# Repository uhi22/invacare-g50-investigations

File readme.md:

# Invacare G50 Investigations

Investigating an electric wheel chair

## Progress

### 2025-01-07: DX-DASH Generation 2 ready for testing

The DX-DASH generation 2 consists of a board containing an STM32 controller, designed in KiCad,
a housing designed in FreeCad and the software designed in the STM CubeIDE.
The DX-DASH gen2 is controlling the Power Module, using either joystick or drive pedal and
direction switch.

[Instruction manual](doc/2025-01-06_DXDASH_installation_und_bedienung.md)

### 2024-10-15: STM32 simulates the UCM and the SLM

Simulating the UCM and the ServoLightModule, the STM32 is able to control
the motor speed directly.

### 2024-10-11: STM32 as UCM-replacement controls all functionality

The STM32 as UCM replacement controls a lot of functionality:
- Wakeup the other modules via the DXBUS
- Control the low beam light and the flashers
- Switch the power module into driving mode and back to idle mode
- Drive motor forwards and backwards using analog joystick input
- Turn the steering servo left and right using analog joystick input
- Send the power module and servo light module to sleep

### 2024-10-02: First spin

The STM32 sends all CAN messages to make the motor spin.

### 2024-09-30: Steering reacts

By sending some half-way proper CAN messages from the STM32 UCM replacement, the servo can be controlled to right-turn.
The motor disables the brake, but does not spin yet. It blinks 12 times.

### 2024-09-26: Controlling the lights works

Using the STM32 "blue pill" and a CAN transceiver, we control the lights via CAN. Due to the disconnected UCM,
the motor controller is stuck in state 0C, and the ServoLightModule in state 0. But nevertheless, low beam and
the turn indicators can be perfectly controlled with a 20ms message "0x040 B0 14 xx".
The ServoLightModule works even with very low battery voltage of 10V in this situation.

### 2024-09-24: STM32 interprets some network variables

Using the STM32 and attached display, we decode some network variables out of the CAN messages,
and show them on the display. 

## Goals

1. Understand the communication on the DX-BUS
2. Replace the original joystick ("UCM") by a self-made box which can control the motor, the lights and the steering.
3. Replace the UCM and the ServoLightModule by a self-made box to control only the motor.

## Pinout of the Power Module

The "Power Module" is a DX-PMB2-SAS, producer "Dynamic Controls", this seems to be the same as the DX-PMB2 mentioned in Ref1.

## Bus Communication

The "DXBUS" consists of four pins:
* Ground
* 24V
* CANH
* CANL

The ground and 24V are directly connected to the battery pins of the power module.

CAN bit time is 9.5µs, this means the CAN baud rate is 105.26 kBaud.
This baud rate can be created (according to STM32 cube IDE) with prescaler=57, T1=3, T2=2, SJW=1, TQ=1583.3ns, bittime=9500ns, 6 TQ per bit, inputClock=36MHz.

### CAN messages

UCM transmit messages (found by adding a separate CAN transceiver to the UCMs CAN_TX line):

* 0x040: The main data message. Contains lot of different sub-data.
* 0x0AA: not very interesting. Always "AA 04".
* 0x29C: "03 00 1A" during run. While turning off, "03 00 10".
* 0x2B4: Constant besides a toggle bit
* 0x2BC: nearly constant, only the last byte changes sometimes.
* 0x3A4: nearly constant, only the last byte changes during shutdown.
* 0x3AC: constant "03 00 1D"

ServoLightingModule transmit messages (found by adding a separate CAN transceiver to the ServoLightingModule CAN_TX line):

* 0x010 is the only transmit message. It contains various sub-messages, e.g.
    * 30 08 00 01 after startup
    * "B0 01 00" and "B0 01 02"
    * "10 00 ....", "12 00 ..."
    * and more

MotorModule transmit messages (all remaining messages which do not come from UCM and ServoLightingModule)
* 0x008 is the only transmit message. It contains various sub-messages, e.g.
    * A3, A1, A4 after startup
    * B0 01 02
    * B0 01 10 0F ...
    * B0 01 10 0C ...
    * B0 01 20 ...
    * B0 01 22
    * B0 01 25 
    * B0 0E ...
    * 30 02 ...
    * and more

```
0x008 B0 01 20 0C B5 0F FF
                   |
                   depends on the supply voltage. A7=22V, B6=24V, C6=26V. 150=19.8V, 200=26.5V 

0x040 B0 93 E1 00 14 00
                      |
                      lights 00=off, 11=light, 02/22 blinker right, 04/44 blinker left, 08/88 hazard flashing

0x040 B0 01 25 90 FF 80
                   |  |
                   |  joystick left/right. 01 is full left. 80 is middle. FF is full right.
                   joystick up/down. 01 is full backwards. 80 is middle, FF is full forward.
                   
0x2B4 03 00 0A
             |
             different values: 02, 0A. And 00 before power-off.

0x2BC 03 00 0F
             |
             different values: 0B, 0F. And 01 before power-off.
```

#### Message types

- First byte B0: "Network Variable announcement". After the B0 there is one byte NV_ID, followed by the content of the
network variable. The length depends on the ID. Afterwards, more {NV_ID, value} pairs may follow as long as there is space left in the CAN frame.
It is confirmed, that the same network variable can be on different position: The light control variable 14 works for controlling the lights in
the following frames in the same way:
    * 0x040 B0 93 E1 00 14 11
    * 0x040 B0 14 11

- First byte 30: "Wanna know". A node sends this message, to request network variable from other nodes.
```
   I'm the motor and...
   |   I wanna know...
   |   |  from node 2 (ServoLightModule)...
   |   |  |     the network variable 11
   |   |  |     |
0x008 30 02 00 11
```
The addressed node responds accordingly with the value of the requested network variable:
```
   I'm the ServoLightModule and...
   |   I want to announce my network variable...
   |   |  number 11...
   |   |  |   has the value 10.
   |   |  |  |
0x010 B0 11 10
```

After the variable number in the "30" message, there is sometimes more data, sometimes not. E.g. "03". Unclear: Is this an additional
network variable number? Or is it a kind of "request type" which selects the cycle time or number of responses or on/off?

- First byte 31: "unsubscribe". Tells the addressed note that it does not need to send the network variable anymore. E.g.
```
   I'm the ServoLightModule and...
   |   I do not need...
   |   |  from node 8 (UCM)...
   |   |  |     the network variable 2E
   |   |  |     |
0x010 31 08 00 2E
```
After this unsubscription, the UCM stops the cyclic transmission of NV 2E.

- First byte 20: unclear. Used in the first messages after startup. 4297725430,00000040,false,Rx,9,8,20,00,00,08,00,00,00,00,
- First byte 23: unclear. E.g. 00000040,false,Rx,9,8,23,00,00,08,FC,80,00,00. Responded by A3.
- First byte 21: similar to 23
- First byte 24: similar to 23

Request-response:
* 4297804953,00000040,false,Rx,9,8,23,00,00,08,FC,80,00,00,  request from the UCM
* 4297805609,00000008,false,Rx,9,1,A3                        response from Motor, where A3 seems to be the response to 23
* 4297806161,00000010,false,Rx,9,1,A3                        response from Servo, where A3 seems to be the response to 23
(and repeated)

again with other number:
* 4297818227,00000040,false,Rx,9,8,21,00,00,08,FC,80,00,00,  request from the UCM
* 4297818888,00000008,false,Rx,9,1,A1                        response from Motor
* 4297819437,00000010,false,Rx,9,1,A1                        response from Servo
(and repeated)

again with other number:
* 4297830564,00000040,false,Rx,9,8,24,00,00,08,FC,40,00,00,  request from the UCM
* 4297832560,00000008,false,Rx,9,1,A4                        response from Motor
* 4297832579,00000010,false,Rx,9,1,A4                        response from Servo
(and repeated)

### Profile changes

If the user changes the driving profile ("gear"), e.g. from 2 to 3, this results in
1. 040: B0,93,63,00,14,00 (once) The UCM announces profile 3.
2. 040: B0,93,E3,00 (repeated each 200ms) The UCM announces profile 3 in an other way.
3. 010: 30,08,00,2C The servo light module requests from the UCM the NV 2C.
4. 040: B0,93,E3,00,14,00,2C,66 UCM provides the NV 2C. Repeated after 200ms.
5. 010: 31,08,00,2C The servo light module stops the subscription of NV 2C.
6. The request/response/unsubscribe continues for other variables.

The end speed (at full joystick way) is parametrized separately for forward and reverse directions. Example profiles,
to demonstrate the speed influence of NV 2C (forward speed) and NV 2F (reverse speed):

```
		/* profiles:
		  1     2     3     4     5  */
		0x10, 0x59, 0x66, 0x73, 0xff, /* NV 0x2C */ /* max speed fwd. 10=very low, ff=high speed */
		0x66, 0x66, 0x73, 0x80, 0x80, /* NV 0x2D */
		0x20, 0x80, 0x80, 0x80, 0x80, /* NV 0x2E */
		0x10, 0x66, 0x66, 0x66, 0xff, /* NV 0x2F */ /* max speed reverse. 10=very low, ff=high speed */
		0x66, 0x66, 0x73, 0x80, 0x80, /* NV 0x30 */
		0x99, 0x99, 0x99, 0x99, 0x99, /* NV 0x31 */
		0xCC, 0xCC, 0xCC, 0xCC, 0xCC, /* NV 0x32 */
		0xB3, 0xB3, 0xB3, 0xB3, 0xB3, /* NV 0x33 */
		0x33, 0x33, 0x4D, 0x4D, 0x4D, /* NV 0x34 */
		0x80, 0x80, 0x99, 0xA6, 0xA6, /* NV 0x35 */
```

These profiles are used only by the ServoLightModule. The motor module is not interested into these profiles. The motor
module is controlled by network variable 0B, which the ServoLightModule provides.

### Error Codes

The PowerModule provides with the network variable 07 some error information:
- 00: no error. No blink code on the UCM.
- 0C: uncoupled the G40 motor. Blink code 3 on the UCM.
- 10: Motor M1 disconnected. Blink code 5 on the UCM.
- (more to be tested)

To use this error reporting, the NV 07 needs to be requested once at the beginning:
`00000010,false,Rx,9,4,30,01,00,07`

## The Wakeup

As long as the system is "off", the DX-BUS still carries 24V battery voltage, and both CAN lines are sitting at ~2.5V.
The system is activated when the user pushes the on/off button on the joystick module ("UCM"). The UCM wakes the other
control units by pulling the CANH to 24V for ~40ms. Afterwards, the UCM sends CAN traffic to keep the other control units
awake. If we apply just the wakeup pulse and do not send any CAN messages, the control units go to sleep again after five seconds.

## The Go-To-Sleep

If the user pushes the on/off button while the system is running, the UDS sends some special messages to send the other control
units to sleep, and stops the CAN communication. (Todo: Details to be described.)
If we just stop sending any messages from the UCM, the ServoLightModule enters an "emergency mode" after some seconds, where
it activats the hazard-flashing.

## Using the ServoLightModule standalone

The ServoLightModule can be used without the PowerModule to control the lights and the steering servo. Several aspects need to be considered to make this work.

1. The CAN termination. The absence of the PowerModule causes a missing CAN termination. We need to add a 510 ohm (or 470ohm) between
CANH and CANL. Additionally, we need a pull-up of the CANH via a diode and 390ohms (in series) to 3.3V, because the CAN transceiver inside
the SLM seems not to be capable of driving the CANH to high; it only pulls the CANL to low. So without additional pull-up on CANH,
a normal CAN transceiver is not able to pick-up the messages of the SLM.

2. The light control. This is the easy part. The SLM listens to the network variable 0x14, which we can announce e.g. with a message `0x040 B0 93 E1 00 14 00`. The light control bits are explained above. The SLM does not need to see the PowerModule for this functionality.

3. The steering servo control. This part is more tricky. To make the steering function work, the SLM needs to see the PowerModule and needs
to go through the corrects states.

    - The UCM and PowerModule must simulate the 23/A3, 21/A1 and 24/A4 sequences during startup.
    - The PowerModule must send the status after the SLM requests it with 010 30 01 00 01.
    - The PowerModule must send the network variables 0F, 0E and 07 after the SLM requested it with 010 30 01 00 0F or 010 30 01 00 0E or 010 30 01 00 07. If the SLM does not receive them, it changes from state 10 (init) to state 0C (error).
    - Even if the SLM now removes the steering brake when entering state 0x25, still the steering only works sporadically. To be further investigated.

## UCM (Joystick Control Module)

CAN_TX: Is the pin 1 of the 74HC02 on the sub-board.

### Diagnostic Connector

according to ref1, this is RS232.

## The Motor Controller (Power Module, PM)

Pinout: 

Motor PWM control:

Park brake control:

* The black park brake wire is grounded.
* The yellow park brake wire is switched to 24V to release the brake. Each 200ms, the PM turns the park brake off for 250µs, most likely for diagnotic purposes.

Current consumption:

* in sleep: 600µA. This means, a 20Ah usable battery capacity lasts for more than 3 years.

## The Motor

* Does does a motor of a G40 work at the motor controller of the G50? Yes.
* How does the "manual clutch switch" work?
    * In the G50 motor, when the user actuates the clutch to push the chair manually, the motor-integrated switch disconnects the *park brake magnet*.
    * In the G40plus motor, the motor integrated switch directly disconnects the *motor*.

## Self-made DXBUS controller

An STM32 development board ("blue pill"), combined with a ILI9341 TFT display and a SN65HVD230 CAN transceiver board and some small additions
is used to send and receive the CAN messages on the DXBUS, and also to send the wakeup pulse.

The 3D model for the printed DXBUS plug is available as [FreeCad model](3d_models/DXBUS_plug.FCStd) and [step file](3d_models/DXBUS_plug.step).

The software (as STM CubeIDE project) is available [here](stm32-tft).

## Open Todos

- [ ] ServoPos shows permanent 0
- [ ] add direction switch and pedal input
- [ ] implement special case "power button during driving"
- [ ] improve CAN scheduling to avoid message losses

## Finished Todos

- [x] Send NV 92 with FF FF in 200ms cycle
- [x] Send the profile (e.g. NV 93 = E1 00)
- [x] Send the parameters of the profile (NVs 2C to 35), after the ServoLight 0x010 requested it, e.g.
    - servoLight requests the 2C from UCM with 00000010,false,Rx,9,4,30,08,00,2C
    - ...
    - servoLight requests the 2E from UCM with 00000010,false,Rx,9,4,30,08,00,2E
    - more general: UCM needs to satisfy all requests (search for 30,08,00)
- [x] Find out how to parametrize the speed
- [x] Reset the CAN controller if it enters bus-off
- [x] Implement UCM start/idle/drive/idle/shutdown state machine
- [x] implement emulation of ServoLightModule, to be able to run the motor control unit without physical ServoLightModule

## Cross References

* [Ref1] System manual for the DXBUS https://www.dynamiccontrols.com/sites/default/files/2018-05/dx-system-manual-issue1.pdf
* [Ref2] European Patent EP0725738A1 (year 1993) https://patents.google.com/patent/EP0725738A1/en
* [Ref3] European Patent EP0725738B1 (year 1993), including schematics, state machines, some network variables. https://patents.google.com/patent/EP0725738B1/en
* [Ref4] SavvyCAN open source CAN logging tool https://www.savvycan.com/
* [Ref5] wifican CAN adaptor via wifi. Adapted to support the 105kBaud of the DXBUS. https://github.com/uhi22/wifican/commit/1e717946a06a594cf2e79b092cbaf7b376e8bb55
* [Ref6] pictures and document collection for the Invacare G50 https://hnng.de/invacare-g50/
* [Ref7] Master Thesis of Markus Schuch / Technikum Wien including a good overview over different wheel chair concepts, and a raspberry-pi based CAN "man in the middle" approach for the DXBUS. https://epub.technikum-wien.at/urn/urn:nbn:at:at-ftw:1-39670

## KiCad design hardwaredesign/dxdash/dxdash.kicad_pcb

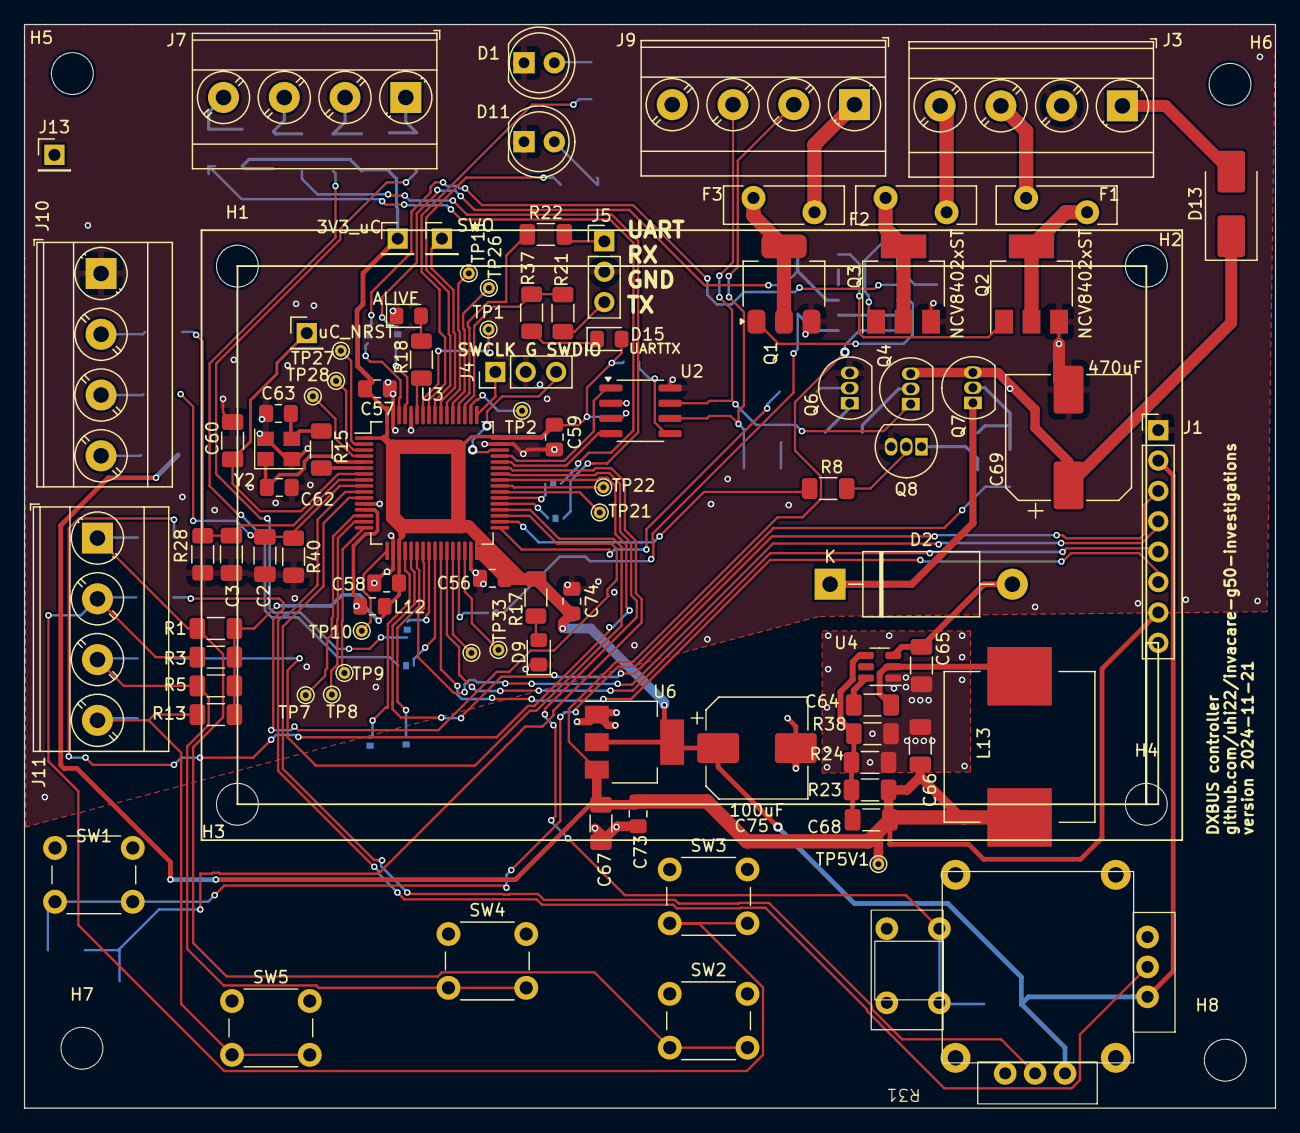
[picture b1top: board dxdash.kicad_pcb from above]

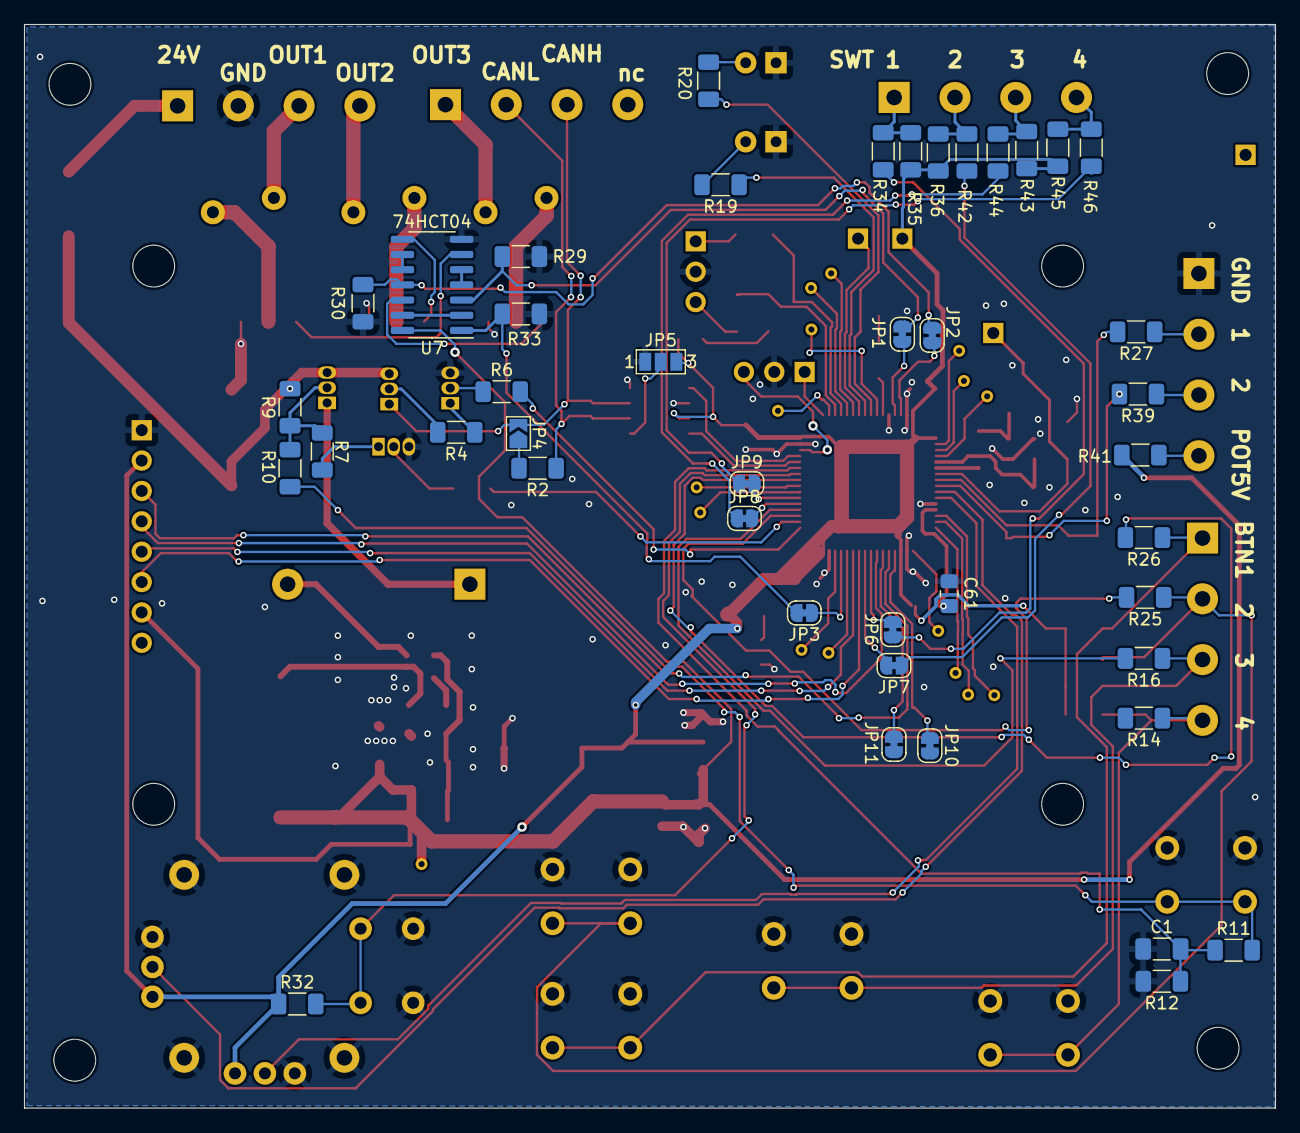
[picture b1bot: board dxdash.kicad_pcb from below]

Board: 2 copper layers, 104.6 x 90.6 mm, 143 parts (43 on the bottom side), 112 nets.

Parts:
C1: 100n; C_1206_3216Metric_Pad1.33x1.80mm_HandSolder
C2, C3, C60, C64: 100nF; C_1206_3216Metric_Pad1.33x1.80mm_HandSolder
C56, C57, C58, C59, C61, C73, C74: 100nF; C_0805_2012Metric_Pad1.18x1.45mm_HandSolder
C62, C63: 22p; C_0805_2012Metric_Pad1.18x1.45mm_HandSolder
C65: 10uF; C_1206_3216Metric_Pad1.33x1.80mm_HandSolder
C66, C67: 22uF; C_1206_3216Metric_Pad1.33x1.80mm_HandSolder
C68: 68pF; C_1206_3216Metric_Pad1.33x1.80mm_HandSolder
C69: 470uF; CP_Elec_10x10
C75: 100uF; CP_Elec_8x10
D1, D11: LED2; LED_D5.0mm
D2: Zener 5V; D_DO-201_P15.24mm_Horizontal
D9: PWR; LED_0805_2012Metric_Pad1.15x1.40mm_HandSolder
D10: ALIVE; LED_0805_2012Metric_Pad1.15x1.40mm_HandSolder
D13: SS54B-HF; D_SMB_Handsoldering
D15: UARTTX; LED_0805_2012Metric_Pad1.15x1.40mm_HandSolder
F1, F2, F3: Polyfuse; Fuse_Bourns_MF-RG400
H1, H2, H3, H4, H5, H6, H7, H8: MountingHole; MountingHole_3.5mm
J1: Conn_01x08_Pin; PinHeader_1x08_P2.54mm_Vertical
J3, J7, J9, J10, J11: Screw_Terminal_01x04; TerminalBlock_Phoenix_MKDS-3-4-5.08_1x04_P5.08mm_Horizontal
J4: DEBUG; PinHeader_1x03_P2.54mm_Vertical
J5: UART; PinHeader_1x03_P2.54mm_Vertical
J13: Conn_01x01_Pin; PinHeader_1x01_P2.54mm_Vertical
J16: uC_NRST; PinHeader_1x01_P2.54mm_Vertical
J17: 3V3_uC; PinHeader_1x01_P2.54mm_Vertical
J18: SWO; PinHeader_1x01_P2.54mm_Vertical
JP1, JP2, JP3, JP6, JP7, JP8, JP9, JP10, JP11: SolderJumper_2_Bridged; SolderJumper-2_P1.3mm_Bridged_RoundedPad1.0x1.5mm
JP4: SolderJumper_2_Open; SolderJumper-2_P1.3mm_Open_TrianglePad1.0x1.5mm
JP5: SolderJumper_3_Open; SolderJumper-3_P1.3mm_Open_Pad1.0x1.5mm_NumberLabels
L12: Bead 600; L_0805_2012Metric_Pad1.15x1.40mm_HandSolder
L13: 10uH; L_Wuerth_WE-PD-Typ-LS_Handsoldering
Q1, Q2, Q3: NCV8402xST; SOT-223
Q4, Q7: BC556; TO-92_Inline
Q6, Q8: BC546; TO-92_Inline
R1, R3, R4, R5, R6, R8, R11, R12, R13, R29, R30, R32, R33, R35, R36, R43, R45: 10k; R_1206_3216Metric_Pad1.30x1.75mm_HandSolder
R2, R17, R18, R19, R20, R37: 1k; R_1206_3216Metric_Pad1.30x1.75mm_HandSolder
R7, R9, R10: 4k7; R_1206_3216Metric_Pad1.30x1.75mm_HandSolder
R14, R16, R25, R26, R27, R28, R34, R39, R40, R42, R44, R46: 47k; R_1206_3216Metric_Pad1.30x1.75mm_HandSolder
R15: 33; R_1206_3216Metric_Pad1.30x1.75mm_HandSolder
R21, R22: 220; R_1206_3216Metric_Pad1.30x1.75mm_HandSolder
R23: 100k; R_1206_3216Metric_Pad1.30x1.75mm_HandSolder
R24: 33k; R_1206_3216Metric_Pad1.30x1.75mm_HandSolder
R31: Joystick; joystickXYButton
R38: 22k; R_1206_3216Metric_Pad1.30x1.75mm_HandSolder
R41: 100; R_1206_3216Metric_Pad1.30x1.75mm_HandSolder
SW1, SW2, SW3, SW4, SW5: SW_Push; SW_PUSH_6mm_H5mm
TP1, TP2, TP7, TP8, TP9, TP10, TP11, TP21, TP22, TP25, TP26, TP27, TP28, TP29, TP33: TestPoint_THTPad_D1.0mm_Drill0.5mm
TP5V1: TP5V; TestPoint_THTPad_D1.0mm_Drill0.5mm
U2: SN65HVD234; SOIC-8_3.9x4.9mm_P1.27mm
U3: STM32F103RETx; LQFP-64_10x10mm_P0.5mm
U4: TPS54302; SOT-23-6
U6: AMS1117-3.3; SOT-223-3_TabPin2
U7: 74HCT04; SO-14_3.9x8.65mm_P1.27mm
Y2: 8MHz; Crystal_SMD_TXC_7M-4Pin_3.2x2.5mm

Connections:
3V3_uC: C56.2, C57.2, C58.2, C59.2, C74.2, C75.1, D15.2 (A), J1.2, J17.1, JP5.3 (B), L12.2, R1.1, R3.1, R5.1, R13.1, R17.1, R31.1 (X1), R31.4 (Y1), R32.1, R35.1, R36.1, R43.1, R45.1, U2.3 (VCC), U3.1 (VBAT), U3.19 (VDD), U3.32 (VDD), U3.48 (VDD), U3.64 (VDD), U6.2 (VO)
5V: C66.2, C67.2, C68.2, C73.2, J1.7, L13.2, R23.1, R41.2, TP5V1.1, U6.3 (VI), U7.14 (VCC)
24V: D13.2 (A), J3.1
24V_P: C69.1, D13.1 (K), Q4.3 (E), Q7.3 (E), R9.2
24V_SWITCHED: C65.2, D2.2 (A), U4.3 (VIN)
/controller/OCS_IN: C62.2, U3.5 (PD0), Y2.1
/controller/OSC_OUT: R15.2, U3.6 (PD1)
BUSWAKE: R6.2, U3.33 (PB12)
CANH: J9.3, JP4.2 (B), Q4.1 (C), U2.7 (CANH)
CANL: J9.2, R2.1, U2.6 (CANL)
CAN_RX: U2.4 (R), U3.44 (PA11)
CAN_TX: U2.1 (D), U3.45 (PA12)
DISPLAY_DC: J1.6, U3.26 (PB0)
DISPLAY_RES: J1.5, U3.27 (PB1)
GND: C1.1, C2.2, C3.2, C56.1, C57.1, C58.1, C59.1, C60.1, C61.1, C62.1, C63.1, C65.1, C66.1, C67.1, C69.2, C73.1, C74.1, C75.2, D1.1 (K), D9.1 (K), D10.1 (K), D11.1 (K), J1.1, J3.2, J4.2, J5.2, J10.1, JP5.1 (A), Q1.3 (S), Q2.3 (S), Q3.3 (S), Q6.3 (E), Q8.3 (E), R12.2, R24.1, R28.1, R29.2, R30.1, R31.3 (X2), R31.6 (Y2), R31.9 (B2), R31.10 (B2.2), R31.11 (GND), R31.12 (GND), R31.13 (GND), R31.14 (GND), R33.2, R38.1, R40.1, SW1.1, SW2.1, SW3.1, SW4.1, SW5.1, U2.2 (GND), U2.8 (Rs), U3.12 (VSSA), U3.18 (VSS), U3.31 (VSS), U3.47 (VSS), U3.60 (BOOT0), U3.63 (VSS), U4.1 (GND), U6.1 (GND), U7.7 (GND), Y2.2, Y2.4
KEEP_ON: R8.2, U3.34 (PB13)
LED2: R19.1, U3.56 (PB4)
LED3: R20.1, U3.57 (PB5)
LED_ALIVE: R18.1, U3.59 (PB7)
unnamed: C63.2, R15.1, Y2.3
unnamed: D1.2 (A), R20.2
unnamed: D2.1 (K), Q7.1 (C)
unnamed: D9.2 (A), R17.2
unnamed: D10.2 (A), R18.2
unnamed: D11.2 (A), R19.2
unnamed: D15.1 (K), R37.2
unnamed: F1.1, Q2.2 (D), Q2.4 (D)
unnamed: F2.1, Q3.2 (D), Q3.4 (D)
unnamed: F3.1, Q1.2 (D), Q1.4 (D)
unnamed: J5.1, R22.2
unnamed: J5.3, R21.2
unnamed: JP1.1 (A), U3.61 (PB8)
unnamed: JP2.1 (A), U3.62 (PB9)
unnamed: JP3.1 (A), U3.29 (PB10)
unnamed: JP4.1 (A), R2.2
unnamed: JP5.2 (C), U2.5 (EN)
unnamed: JP6.2 (B), U3.24 (PC4)
unnamed: JP7.2 (B), U3.25 (PC5)
unnamed: JP8.2 (B), U3.37 (PC6)
unnamed: JP9.2 (B), U3.38 (PC7)
unnamed: Q1.1 (G), U7.12
unnamed: Q2.1 (G), U7.6
unnamed: Q3.1 (G), U7.8
unnamed: Q4.2 (B), R4.2
unnamed: Q6.2 (B), R6.1
unnamed: Q6.1 (C), R4.1
unnamed: Q7.2 (B), R7.2, R9.1, R10.1
unnamed: Q8.2 (B), R8.1
unnamed: Q8.1 (C), R7.1
unnamed: R10.2, R11.2, SW1.2
unnamed: TP7.1, U3.14 (PA0)
unnamed: TP8.1, U3.15 (PA1)
unnamed: TP9.1, U3.16 (PA2)
unnamed: TP10.1, U3.17 (PA3)
unnamed: TP2.1, U3.50 (PA15)
unnamed: TP25.1, U3.28 (PB2)
unnamed: TP1.1, U3.58 (PB6)
unnamed: TP33.1, U3.30 (PB11)
unnamed: TP21.1, U3.39 (PC8)
unnamed: TP22.1, U3.40 (PC9)
unnamed: TP26.1, U3.53 (PC12)
unnamed: TP27.1, U3.2 (PC13)
unnamed: TP28.1, U3.3 (PC14)
unnamed: TP29.1, U3.4 (PC15)
unnamed: TP11.1, U3.54 (PD2)
unnamed: C61.2, L12.1, U3.13 (VDDA)
unnamed: C64.2, U4.6 (BOOT)
unnamed: C68.1, R23.2, R24.2, R38.2, U4.4 (FB)
unnamed: C64.1, L13.1, U4.2 (SW)
unnamed: U7.4, U7.5
unnamed: U7.9, U7.10
unnamed: U7.2, U7.13
OUT1_LS: F1.2, J3.3
OUT2_LS: F2.2, J3.4
OUT3_LS: F3.2, J9.1
OUT_CONTROL1: JP1.2 (B), R29.1, U7.3
OUT_CONTROL2: JP2.2 (B), R30.2, U7.11
OUT_CONTROL3: JP3.2 (B), R33.1, U7.1
SPI1_CLK: J1.3, U3.21 (PA5)
SPI1_MISO: JP11.1 (A), U3.22 (PA6)
SPI1_MOSI: J1.4, U3.23 (PA7)
SPI1_NSS: JP10.1 (A), U3.20 (PA4)
SWCLK: J4.1, U3.49 (PA14)
SWDIO: J4.3, U3.46 (PA13)
SWO: J18.1, U3.55 (PB3)
UART4_RX: R22.1, U3.52 (PC11)
UART4_TX: R21.1, R37.1, U3.51 (PC10)
button1: J11.1, R1.2, R26.1, SW2.2
button2: J11.2, R3.2, R25.1, SW3.2
button3: J11.3, R5.2, R16.1, SW4.2
button4: J11.4, R13.2, R14.1, SW5.2
pot1: J10.2, R27.1
pot2: J10.3, R39.1
pot5V: J10.4, R41.1
switch1: J7.1, R34.1, R35.2
switch2: J7.2, R36.2, R42.1
switch3: J7.3, R43.2, R44.1
switch4: J7.4, R45.2, R46.1
uC_NRST: C60.2, J16.1, U3.7 (NRST)
uC_button1: R26.2, U3.41 (PA8)
uC_button2: R25.2, U3.35 (PB14)
uC_button3: R16.2, U3.36 (PB15)
uC_joystickX: R31.2 (XM), U3.10 (PC2)
uC_joystickY: R31.5 (YM), U3.11 (PC3)
uC_joystickbutton: R31.7 (B1), R31.8 (B1.2), R32.2, U3.42 (PA9)
uC_pot1: C3.1, R27.2, R28.2, U3.8 (PC0)
uC_pot2: C2.1, R39.2, R40.2, U3.9 (PC1)
uC_pwr_button: C1.2, R11.1, R12.1, U3.43 (PA10)
uC_switch1: JP6.1 (A), R34.2
uC_switch2: JP7.1 (A), R42.2
uC_switch3: JP8.1 (A), R44.2
uC_switch4: JP9.1 (A), R46.2

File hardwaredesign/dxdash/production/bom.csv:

Designator,Footprint,Quantity,Value,LCSC Part #
C1,1206,1,100n,C14663
"C2, C3, C60, C64",1206,4,100nF,C14663
"C56, C57, C58, C59, C61, C73, C74",0805,7,100nF,C14663
"C62, C63",0805,2,22p,C1679
C65,1206,1,10uF,C14663
"C66, C67",1206,2,22uF,C14663
C68,1206,1,68pF,C14663
C69,CP_Elec_10x10,1,470uF,
C75,CP_Elec_8x10,1,100uF,
"D1, D11",LED_D5.0mm,2,LED2,
D10,0805,1,ALIVE,
D13,D_SMB_Handsoldering,1,SS54B-HF,
D15,0805,1,UARTTX,
D2,D_DO-201_P15.24mm_Horizontal,1,Zener 5V,
D9,0805,1,PWR,
"F1, F2, F3",Fuse_Bourns_MF-RG400,3,Polyfuse,
J1,PinHeader_1x08_P2.54mm_Vertical,1,Conn_01x08_Pin,
"J10, J11, J3, J7, J9",TerminalBlock_Phoenix_MKDS-3-4-5.08_1x04_P5.08mm_Horizontal,5,Screw_Terminal_01x04,
J13,PinHeader_1x01_P2.54mm_Vertical,1,Conn_01x01_Pin,
J16,PinHeader_1x01_P2.54mm_Vertical,1,uC_NRST,
J17,PinHeader_1x01_P2.54mm_Vertical,1,3V3_uC,
J18,PinHeader_1x01_P2.54mm_Vertical,1,SWO,
J4,PinHeader_1x03_P2.54mm_Vertical,1,DEBUG,
J5,PinHeader_1x03_P2.54mm_Vertical,1,UART,
L12,0805,1,Bead 600,C1002
L13,L_Wuerth_WE-PD-Typ-LS_Handsoldering,1,10uH,C162588
"Q1, Q2, Q3",SOT-223,3,NCV8402xST,
"Q4, Q7",TO-92_Inline,2,BC556,
"Q6, Q8",TO-92_Inline,2,BC546,
"R1, R13, R29, R3, R30, R32, R33, R35, R36, R43, R45, R5",1206,12,10k,C25804
"R10, R7, R9",1206,3,4k7,C22978
"R11, R12, R4, R6, R8",1206,5,10k,C22978
"R14, R16, R25, R26, R27, R28, R34, R39, R40, R42, R44, R46",1206,12,47k,C25804
R15,1206,1,33,C23140
"R17, R18, R19, R2, R20, R37",1206,6,1k,C22978
"R21, R22",1206,2,220,C22978
R23,1206,1,100k,C25804
R24,1206,1,33k,C25804
R31,joystickXYButton,1,Joystick,
R38,1206,1,22k,C25804
R41,1206,1,100,
"SW1, SW2, SW3, SW4, SW5",SW_PUSH_6mm_H5mm,5,SW_Push,
"TP1, TP10, TP11, TP2, TP21, TP22, TP25, TP26, TP27, TP28, TP29, TP33, TP7, TP8, TP9",TestPoint_THTPad_D1.0mm_Drill0.5mm,15,~,
TP5V1,TestPoint_THTPad_D1.0mm_Drill0.5mm,1,TP5V,
U2,SOIC-8_3.9x4.9mm_P1.27mm,1,SN65HVD234,
U3,LQFP-64_10x10mm_P0.5mm,1,STM32F103RETx,
U4,SOT-23-6,1,TPS54302,
U6,SOT-223-3_TabPin2,1,AMS1117-3.3,
U7,SO-14_3.9x8.65mm_P1.27mm,1,74HCT04,
Y2,Crystal_SMD_TXC_7M-4Pin_3.2x2.5mm,1,8MHz,tbd

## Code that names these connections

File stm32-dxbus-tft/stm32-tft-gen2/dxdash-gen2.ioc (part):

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Mcu.Name=STM32F103R(C-D-E)Tx
Mcu.Package=LQFP64
Mcu.UserName=STM32F103RETx
PA0-WKUP.Signal=GPIO_Input
PA10.Signal=GPIO_Input
PA11.Mode=CAN_Activate
PA11.Signal=CAN_RX
PA12.Mode=CAN_Activate
PA12.Signal=CAN_TX
PA5.Mode=TX_Only_Simplex_Unidirect_Master
PA5.Signal=SPI1_SCK
PA6.Signal=SPI1_MISO
PA7.Mode=TX_Only_Simplex_Unidirect_Master
PA7.Signal=SPI1_MOSI
PA8.Signal=GPIO_Input
PA9.Signal=GPIO_Input
PB0.Signal=GPIO_Output
PB1.Signal=GPIO_Output
PB10.Signal=GPIO_Output
PB11.Signal=GPIO_Output
PB12.Signal=GPIO_Output
PB13.Signal=GPIO_Output
PB14.Signal=GPIO_Input
PB15.Signal=GPIO_Input
PB2.Signal=GPIO_Output
PB3.Signal=GPIO_Output
PB4.Signal=GPIO_Output
PB5.Signal=GPIO_Output
PB6.Signal=GPIO_Output
PB7.Signal=GPIO_Output
PB8.Signal=GPIO_Output
PB9.Signal=GPIO_Output
PC0.Signal=ADCx_IN10
PC1.Signal=ADCx_IN11
PC10.Signal=UART4_TX
PC11.Signal=UART4_RX
PC12.Signal=GPIO_Output
PC2.Signal=ADCx_IN12
PC3.Signal=ADCx_IN13
PC4.Signal=GPIO_Input
PC5.Signal=GPIO_Input
PC6.Signal=GPIO_Input
PC7.Signal=GPIO_Input
PC8.Signal=GPIO_Output
PC9.Signal=GPIO_Output
PD0-OSC_IN.Mode=HSE-External-Oscillator
PD0-OSC_IN.Signal=RCC_OSC_IN
PD1-OSC_OUT.Mode=HSE-External-Oscillator
PD1-OSC_OUT.Signal=RCC_OSC_OUT
PD2.Signal=GPIO_Output
RCC.SYSCLKFreq_VALUE=72000000
RCC.SYSCLKSource=RCC_SYSCLKSOURCE_PLLCLK
board=custom

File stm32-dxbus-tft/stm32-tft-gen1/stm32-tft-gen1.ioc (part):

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Mcu.Name=STM32F103C(8-B)Tx
Mcu.Package=LQFP48
Mcu.UserName=STM32F103C8Tx
PA0-WKUP.Signal=ADCx_IN0
PA1.Signal=ADCx_IN1
PA10.Signal=GPIO_Input
PA11.Mode=CAN_Activate
PA11.Signal=CAN_RX
PA12.Mode=CAN_Activate
PA12.Signal=CAN_TX
PA13.Mode=Serial_Wire
PA13.Signal=SYS_JTMS-SWDIO
PA14.Mode=Serial_Wire
PA14.Signal=SYS_JTCK-SWCLK
PA2.Signal=ADCx_IN2
PA3.Signal=ADCx_IN3
PA5.Mode=TX_Only_Simplex_Unidirect_Master
PA5.Signal=SPI1_SCK
PA7.Mode=TX_Only_Simplex_Unidirect_Master
PA7.Signal=SPI1_MOSI
PA8.GPIOParameters=GPIO_PuPd
PA8.GPIO_PuPd=GPIO_PULLUP
PA8.Signal=GPIO_Input
PA9.GPIOParameters=GPIO_PuPd
PA9.GPIO_PuPd=GPIO_PULLUP
PA9.Signal=GPIO_Input
PB0.Signal=GPIO_Output
PB1.Signal=GPIO_Output
PB10.Signal=GPIO_Output
PB12.Signal=GPIO_Output
PB13.Signal=GPIO_Output
PB14.GPIOParameters=GPIO_PuPd
PB14.GPIO_PuPd=GPIO_PULLUP
PB14.Signal=GPIO_Input
PB15.GPIOParameters=GPIO_PuPd
PB15.GPIO_PuPd=GPIO_PULLUP
PB15.Signal=GPIO_Input
PC13-TAMPER-RTC.Signal=GPIO_Output
PD0-OSC_IN.Mode=HSE-External-Oscillator
PD0-OSC_IN.Signal=RCC_OSC_IN
PD1-OSC_OUT.Mode=HSE-External-Oscillator
PD1-OSC_OUT.Signal=RCC_OSC_OUT
RCC.SYSCLKFreq_VALUE=72000000
RCC.SYSCLKSource=RCC_SYSCLKSOURCE_PLLCLK
board=custom

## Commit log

2024-09-21 added some CAN messages
2024-09-22 docu: added more references
2024-09-22 docu: added wakeup plots and CAN logs
2024-09-24 added display software to show some network variables
2024-09-24 some CAN transmit messages. Docu: message details.
2024-09-25 docu: added some references
2024-09-25 more transmit messages
2024-09-26 stm32 controls the lights
2024-09-30 docu: added request message
2024-09-30 send wakeup pulse. Send CAN messages. Shortly unlocking the brake.
2024-09-30 steering reacts, motor not
2024-09-30 docu: update progress
2024-09-30 added more cyclic messages
2024-10-02 docu: added todos
2024-10-02 software and docu for milestone FIRST SPIN
2024-10-03 fix/improvement for joystick simulation
2024-10-03 docu: added goals, wakeup, sleep, pictures
2024-10-04 docu: pictures and motor pinout
2024-10-04 docu: park brake
2024-10-04 CAN: automatic bus-off recovery. No automatic retransmission.
2024-10-04 clarified setup of max speed via the profile variables
2024-10-04 docu: todo resolved
2024-10-04 docu: unsubscribe
2024-10-04 docu: typos corrected
2024-10-07 added ADC conversion, added logs
2024-10-07 fix: correct clock. Feature: read joystick, and control motor and servo with it.
2024-10-07 preparation for network variable decoder
2024-10-08 read buttons. control light and flashers with buttons.
2024-10-09 on/off button works
2024-10-09 docu: added Ref7
2024-10-11 flasher buttons cleanup
2024-10-11 preparation for controlled shutdown sequence
2024-10-11 state change between driving and standby works. Shutdown works.
2024-10-11 docu: status and todos
2024-10-14 prepared simulation of the ServoLightModule
2024-10-15 simulated UCM and simulated SLM are controlling the motor
2024-10-16 docu: added pictures and 3D model, extended readme
2024-10-22 first draft of dxdash schematic and board
2024-11-12 controller board added features
2024-11-13 added joystick
2024-11-14 added polyfuses
2024-11-15 added screw terminals
2024-11-18 added switch inputs. Layout preparation.
2024-11-19 more layout
2024-11-19 layout work in progress
2024-11-21 board: layout finished
2024-12-09 dxdash: corrected some resistor values. Added todos.
2024-12-09 re-arranged STM32 projects into gen1 and gen2
2024-12-09 gen2: integrated hardwareabstraction, scheduler, buttons, powremanager, turnIndicator
2024-12-10 gen2: added display
2024-12-11 added drivingLight. Routed turn indicators to power outputs.
2024-12-11 added analog inputs. Show analog and buttons on status page.
2024-12-11 all switches and buttons in buttonfield
2024-12-11 added CAN, UCM and SLM. Motor spins, controlled by analog joystick.
2024-12-11 fix double speed of the turn indicator
2024-12-12 gen1 TFT display for controlling the SLM
2024-12-16 gen1: interrupt-driven CAN transmit. PowerModule emulation. Steering works sporadically with emulated PowerModule.
2024-12-29 gen2: interrupt-based CAN transmission. Splash screen.
2024-12-29 gen2: improved TX queue handling
2024-12-30 gen2: added debug pins
2024-12-30 gen2: Fix: enable CAN auto-retransmission to avoid message loss. Feature: select creepmode with joystick X
2025-01-02 gen2 features: error bar. Drive pedal. Voltage display and lowvoltage detection.
2025-01-03 gen2: decode error codes of the PowerModule. Show creepmode and direction.
2025-01-04 fix: select unused controller pin for unused chipselect of the display, to avoid out3 flickering.
2025-01-07 docu for gen2
2025-01-07 gen2: create hex file. docu: gen2 status
2025-01-07 corrected typo
2025-01-07 docu: typos
2025-01-14 fix: decode network variables of the powermodule independent of their position
2025-01-14 added release folder
2025-01-14 docu: added download link for gen2 firmware
2025-01-14 gen2: added symbols for turn indicators and light
2025-01-17 docu: sleep current of the power module
